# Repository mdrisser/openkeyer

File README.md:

# OpenKeyer
## Overview
OpenKeyer is an open source, open hardware, modular morse code keyer, built around an Arduino Nano, or compatible, microcontroller. The modular nature of OpenKeyer allows the builder to easily configure his/her OpenKeyer build to suit their needs/desires.

## Modules
The core module and the only required one, is the microcontroller (MCU), all of the other modules connect to the MCU and are controlled by it.

The other modules are:
- Display: This allows easy access to the menu(s), and shows the current code speed. The display is listed as a module simply because there will be support for different display modules, depending on the builder's preference and/or budget. The display can be a 2 or 4 line LCD display, an OLED display or any other type of display provided that the proper code is written to support it. While it is listed as a module, it really should be considered a necessary part of the keyer due to its functionality.
- Twin-T Oscillator: Creates a pure sine wave, which is fed into an audio amplifier, the resulting sound is then played through the onboard speaker, an external speaker or a set of headphones.
- Square-wave oscillator: Uses a 555 timer to produce the tone. Not as pleasant to listen to as a sine wave oscillator, but I will be providing the schematics to incorporate it anyway.
- LED Indicator: Provides a visual indication of the code elements being sent.
- Battery Module: Provides power to the keyer through the use of batteries, allowing the keyer to be more portable.
- Memory: Will allow for storing and replaying morse code strings, such as call sign, SKCC/FISTS/NAQCC number, etc.

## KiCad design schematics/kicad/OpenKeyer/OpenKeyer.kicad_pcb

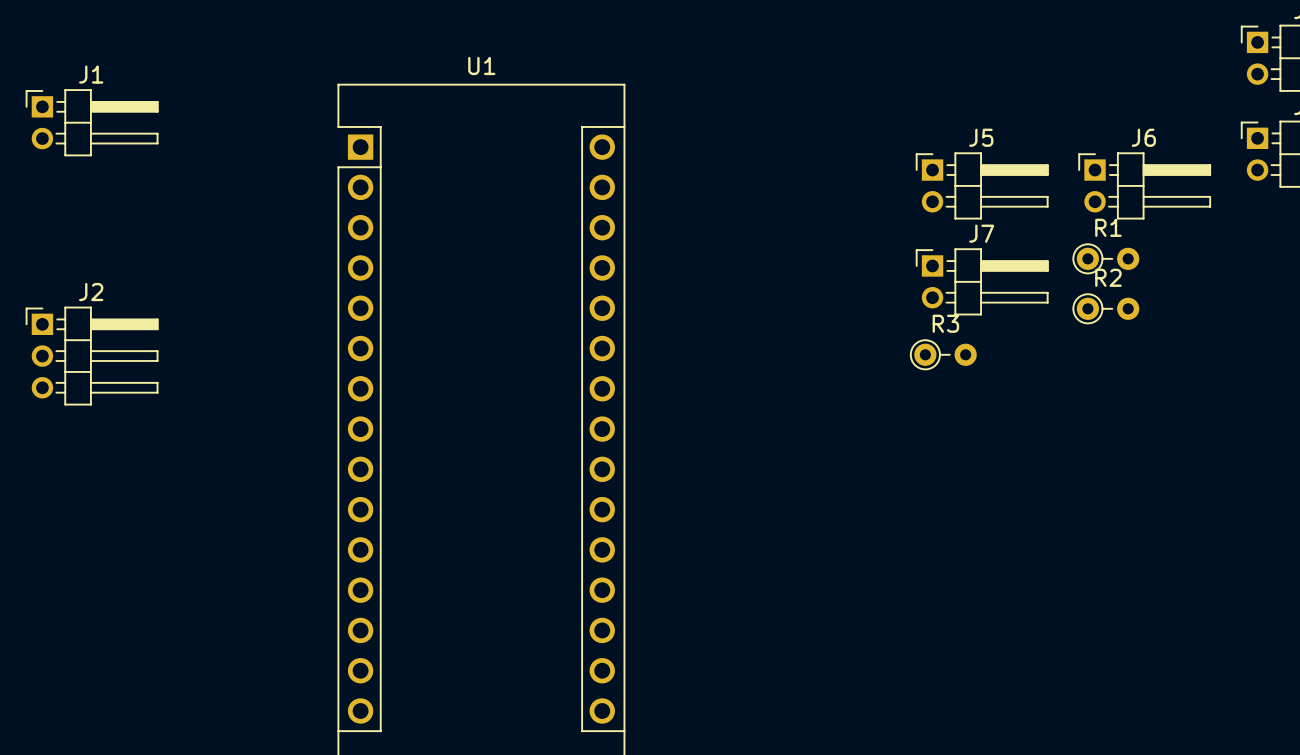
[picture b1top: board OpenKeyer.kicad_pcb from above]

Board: 2 copper layers, 11 parts (0 on the bottom side), 9 nets, no tracks yet.

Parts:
J1: Error Indicator; PinHeader_1x02_P2.00mm_Horizontal
J2: Keyer; PinHeader_1x03_P2.00mm_Horizontal
J3: Oscillator; PinHeader_1x02_P2.00mm_Horizontal
J4: Visual Indicator; PinHeader_1x02_P2.00mm_Horizontal
J5: I2C Bus; PinHeader_1x02_P2.00mm_Horizontal
J6: VIN; PinHeader_1x02_P2.00mm_Horizontal
J7: PWR LED; PinHeader_1x02_P2.00mm_Horizontal
R1, R2, R3: 220; R_Axial_DIN0204_L3.6mm_D1.6mm_P2.54mm_Vertical
U1: Arduino_Nano_v3.x; Arduino_Nano

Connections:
unnamed: J1.1, R1.2
unnamed: J1.2, J3.2, J4.2, J6.2, J7.2, U1.4
unnamed: J3.1, R2.1, U1.15
unnamed: J4.1, R2.2
unnamed: J5.1, U1.23
unnamed: J5.2, U1.24
unnamed: J7.1, R3.1
unnamed: R1.1, U1.6
unnamed: R3.2, U1.30

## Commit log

2022-01-19 Initial Upload
    Initial upload of files to the repository
2022-01-26 Inital Code Upload
2022-02-01 No Summary
    Just syncing between the laptop and desktop
2022-03-10 Update README.md
    Added info about displays; added info about square wave oscillator
2022-03-10 Update README.md
    Added info about memory module
2022-03-10 Re-organization
    Re-organized source code folder, moved C++ into a sub folder, added micropython folder.
2022-03-22 Added more information to the README.md file
